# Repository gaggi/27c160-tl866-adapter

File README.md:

# 27c160-tl866-adapter
Adapter to Program 27c160, 27c322, 27c400 and 27c800 EPROM´s on the popular TL866 Universal Programmer from Autoelectric.

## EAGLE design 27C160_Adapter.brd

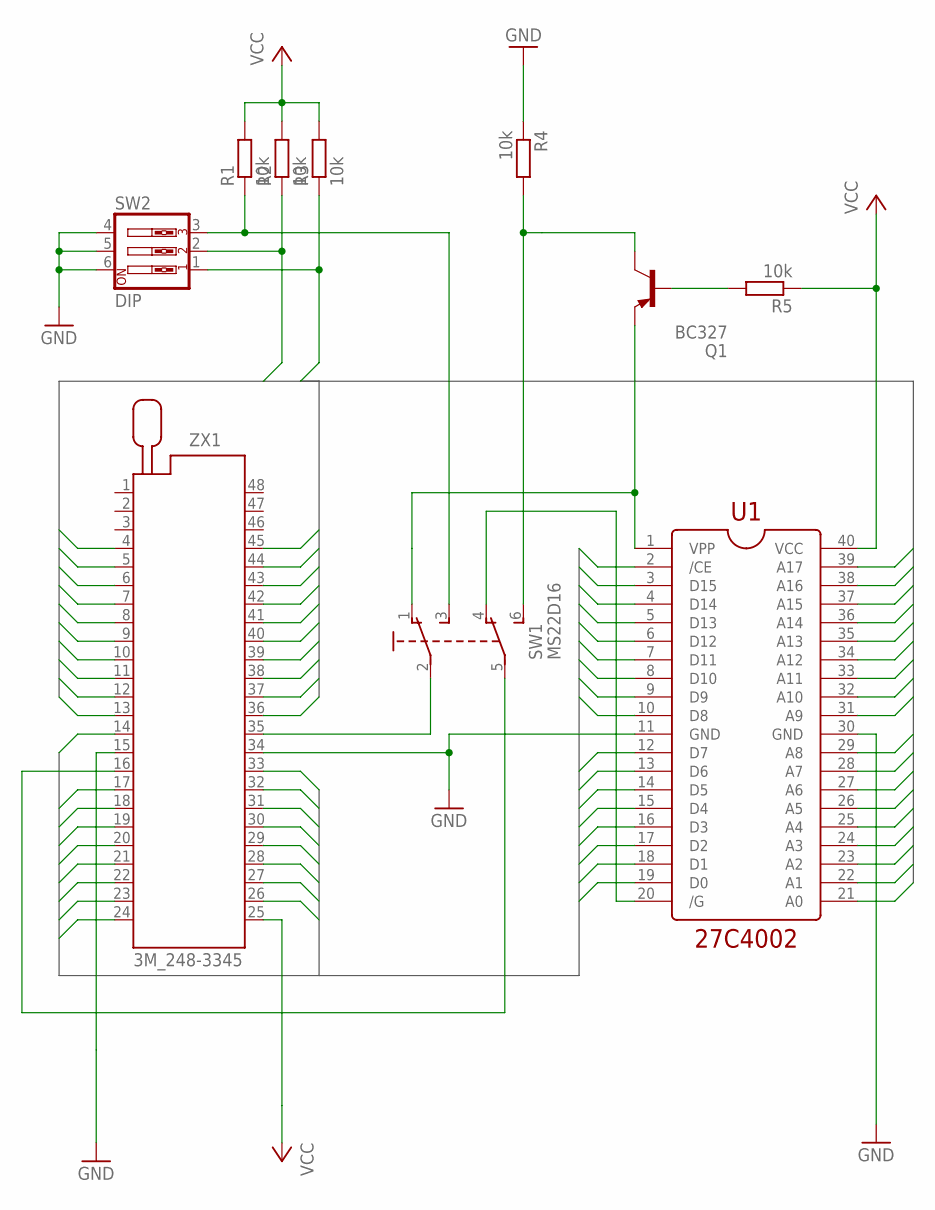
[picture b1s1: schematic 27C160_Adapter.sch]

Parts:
Q1: BC327; TO92-EBC
R1, R2, R3, R4, R5: 10k; 0207/10
SW1: MS22D16
SW2: DIP; EDG-03
U1: 27C4002
ZX1: 3M_248-3345

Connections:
A0: U1.21 (A0), ZX1.13
A1: U1.22 (A1), ZX1.12
A2: U1.23 (A2), ZX1.11
A3: U1.24 (A3), ZX1.10
A4: U1.25 (A4), ZX1.9
A5: U1.26 (A5), ZX1.8
A6: U1.27 (A6), ZX1.7
A7: U1.28 (A7), ZX1.6
A8: U1.29 (A8), ZX1.44
A9: U1.31 (A9), ZX1.43
A10: U1.32 (A10), ZX1.42
A11: U1.33 (A11), ZX1.41
A12: U1.34 (A12), ZX1.40
A13: U1.35 (A13), ZX1.39
A14: U1.36 (A14), ZX1.38
A15: U1.37 (A15), ZX1.37
A16: U1.38 (A16), ZX1.36
A17: U1.39 (A17), ZX1.5
A18: R3.1, SW2.1, ZX1.4
A19: R2.1, SW2.2, ZX1.45
A20: R1.1, SW1.3 (S), SW2.3
D0: U1.19 (D0), ZX1.17
D1: U1.18 (D1), ZX1.19
D2: U1.17 (D2), ZX1.21
D3: U1.16 (D3), ZX1.23
D4: U1.15 (D4), ZX1.26
D5: U1.14 (D5), ZX1.28
D6: U1.13 (D6), ZX1.30
D7: U1.12 (D7), ZX1.32
D8: U1.10 (D8), ZX1.18
D9: U1.9 (D9), ZX1.20
D10: U1.8 (D10), ZX1.22
D11: U1.7 (D11), ZX1.24
D12: U1.6 (D12), ZX1.27
D13: U1.5 (D13), ZX1.29
D14: U1.4 (D14), ZX1.31
D15: U1.3 (D15), ZX1.33
E: U1.2 (/CE), ZX1.14
GND: R4.1, SW2.4, SW2.5, SW2.6, U1.11 (GND), U1.30 (GND), ZX1.15, ZX1.34
unnamed: Q1.B, R5.2
unnamed: SW1.2, ZX1.35
unnamed: Q1.C, R4.2, SW1.6 (S1)
unnamed: SW1.4 (O1), U1.20 (/G)
unnamed: SW1.5 (P1), ZX1.16
VCC: R1.2, R2.2, R3.2, R5.1, U1.40 (VCC), ZX1.25
VPP: Q1.E, SW1.1 (O), U1.1 (VPP)

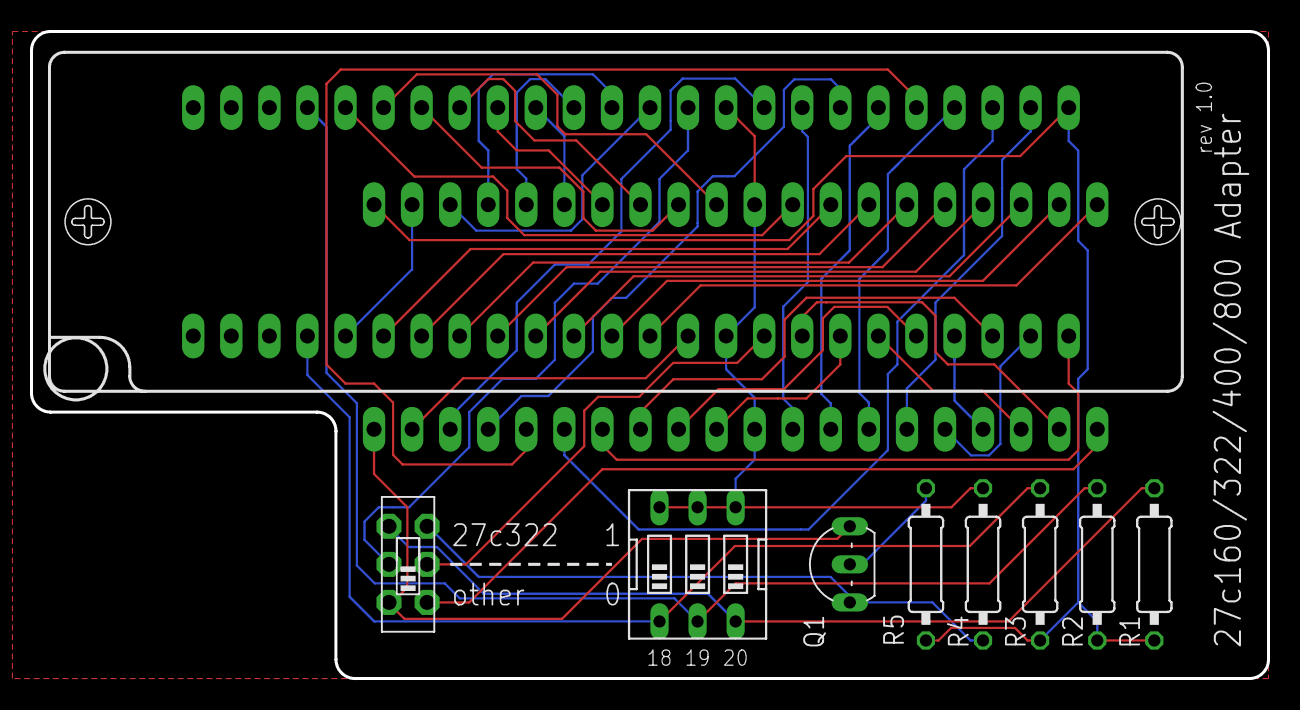
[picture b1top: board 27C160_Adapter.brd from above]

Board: 2 copper layers, 82.5 x 43.2 mm, 10 parts (0 on the bottom side), 46 nets.

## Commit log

2016-08-09 Initial Release
2016-08-10 Added German Manual
2017-07-28 Converting from Eagle to KiCad
    Done the converting and created a 2x1 Panel for use with the chinese 10x10cm PCB services.
2017-09-06 Added .gitignore file
